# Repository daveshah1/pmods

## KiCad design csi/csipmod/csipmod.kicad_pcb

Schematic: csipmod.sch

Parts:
C1, C3: 1µ; C_0805_2012Metric
C2: 100p; C_0402_1005Metric
C4: 10µ; C_0805_2012Metric
J1: PMOD_1A; PMOD_2x06_2.54mm
J2: PMOD_1B; PMOD_2x06_2.54mm
P1: PICAM; 1-1734248-5
R1, R2, R4, R5, R25: 10k; R_0402_1005Metric
R3: 200k; R_0402_1005Metric
R6, R10, R13, R14, R17, R18, R19, R20, R21, R22, R23: DNP; R_0402_1005Metric
R7, R8, R11, R12, R15, R16: 0; R_0402_1005Metric
R9: 220; R_0402_1005Metric
R24: 33k; R_0402_1005Metric
R26, R27, R28: 100; R_0402_1005Metric
R29: 0R; R_0805_2012Metric
U1: LD3985M18R_SOT23; SOT-23-5
U2: PCA9306; SSOP-8_2.95x2.8mm_P0.65mm

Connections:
+1V8: C3.1, R1.1, R2.1, U1.5 (VOUT), U2.2
+3V3: C1.1, J1.6, J1.12, J2.6, J2.12, R3.1, R4.1, R5.1, R24.1, R29.2, U1.1 (VIN), U1.3 (INH)
/CAM_ENABLE: J1.7, P1.11
/CAM_SCL: P1.13, R1.2, U2.3
/CAM_SDA: P1.14, R2.2, U2.4
/CCLK+: P1.9, R16.1, R17.2, R23.1, R28.2
/CCLK-: P1.8, R14.1, R15.1, R22.2, R28.1
/CD0+: P1.3, R8.1, R9.2, R19.1, R26.2
/CD0-: P1.2, R6.1, R7.1, R18.2, R26.1
/CD1+: P1.6, R12.1, R13.2, R21.1, R27.2
/CD1-: P1.5, R10.1, R11.1, R20.2, R27.1
/FPGA_SCL: J2.10, R4.2, U2.6
/FPGA_SDA: J2.3, R5.2, U2.5
/HSCLK+: J2.9, R16.2
/HSCLK-: J2.4, R15.2
/HSD0+: J2.7, R8.2
/HSD0-: J2.2, R7.2
/HSD1+: J2.8, R12.2
/HSD1-: J2.1, R11.2
/LPCLK+: J1.2, R17.1
/LPCLK-: J1.1, R14.2
/LPD0+: J1.4, R9.1
/LPD0-: J1.3, R6.2
/LPD1+: J1.10, R13.1
/LPD1-: J1.9, R10.2
/LPDREF: J1.8, R24.2, R25.1
GND: C1.2, C2.2, C3.2, C4.2, J1.5, J1.11, J2.5, J2.11, P1.1, P1.4, P1.7, P1.10, R18.1, R19.2, R20.1, R21.2, R22.1, R23.2, R25.2, U1.2 (GND), U2.1
unnamed: C2.1, R3.2, U2.7, U2.8
unnamed: C4.1, P1.15, R29.1

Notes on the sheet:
*DNP
*51
*120
*22
NOTE Default values are for camera --> FPGA Values with * are for FPGA --> Pi
PMODs pairs for icebreaker use only

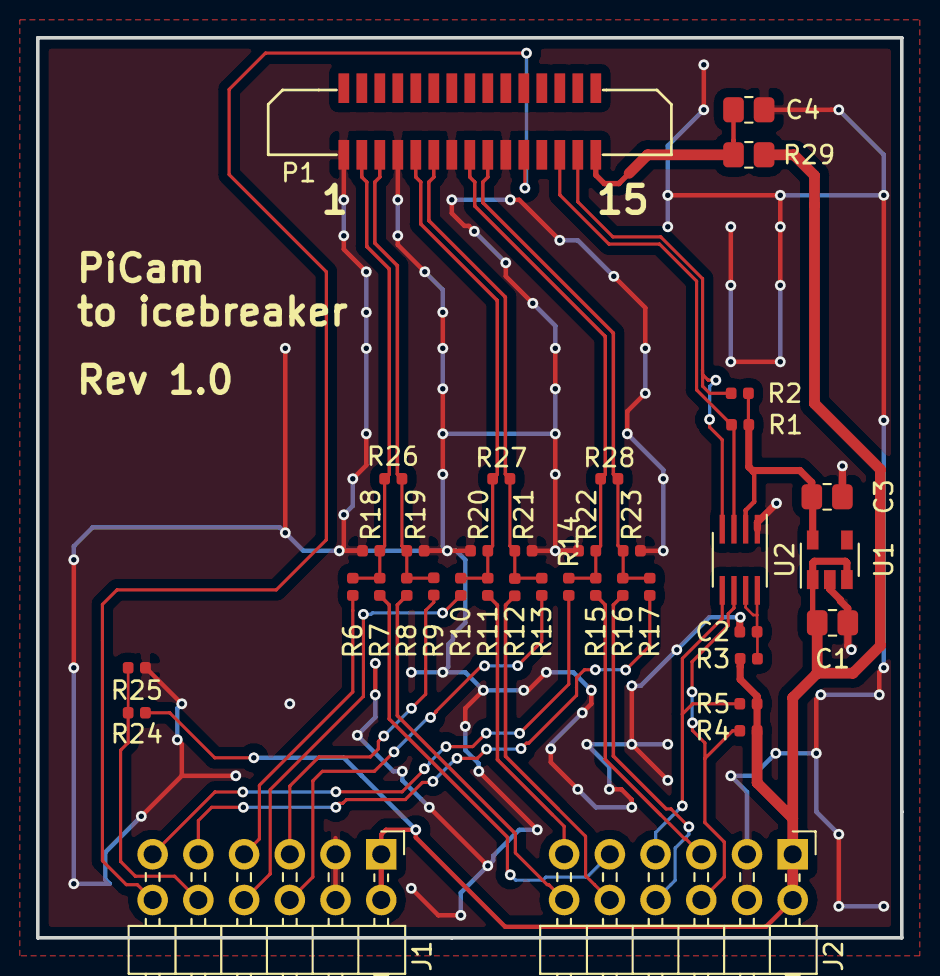
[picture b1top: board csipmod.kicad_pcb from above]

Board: 4 copper layers, 48.0 x 50.0 mm, 38 parts (0 on the bottom side), 29 nets.

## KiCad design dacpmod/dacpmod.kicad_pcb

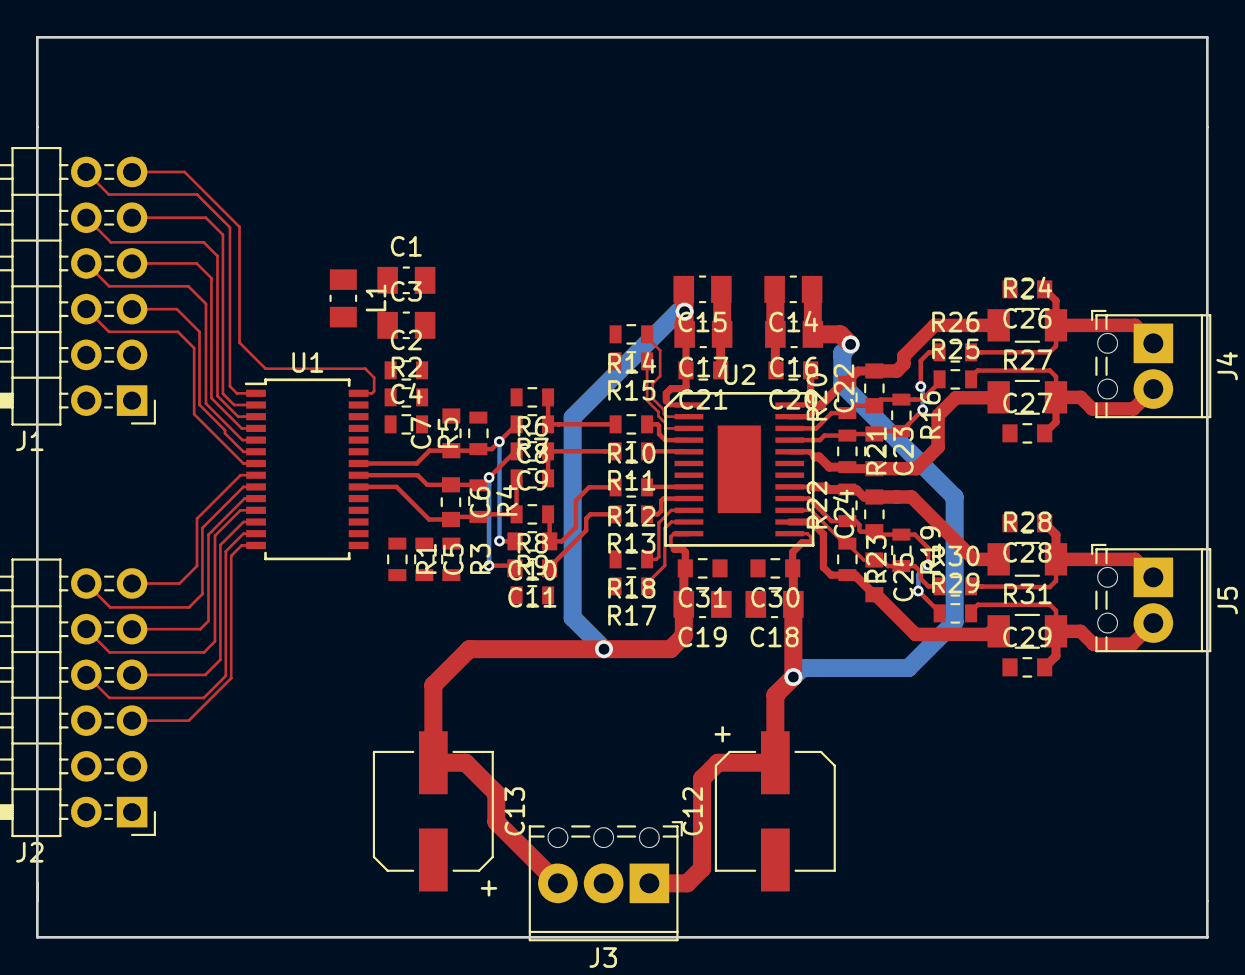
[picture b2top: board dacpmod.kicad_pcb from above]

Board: 2 copper layers, 65.0 x 50.0 mm, 71 parts (1 on the bottom side), 51 nets.

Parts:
C1, C3: 4.7µ; C_0805_2012Metric_Pad1.15x1.50mm_HandSolder
C2, C4, C5, C8, C9: 100n; C_0603_1608Metric
C6, C7, C10, C11, C22, C23, C24, C25, C26, C27, C28, C29: DNP; C_0603_1608Metric_Pad0.84x1.00mm_HandSolder
C12, C13: 100u; CP_Elec_6.3x5.8
C14, C15: 1µ; C_0805_2012Metric_Pad1.15x1.50mm_HandSolder
C16, C17, C18, C19: 100n; C_0805_2012Metric_Pad1.15x1.50mm_HandSolder
C20, C21, C30, C31: 10n; C_0603_1608Metric_Pad0.84x1.00mm_HandSolder
J1: PMOD1; PMOD_2x06_2.54mm
J2: PMOD2; PMOD_2x06_2.54mm
J3: POWER; TerminalBlock_Phoenix_MPT-0,5-3-2.54_1x03_P2.54mm_Horizontal
J4, J5: OUT; TerminalBlock_Phoenix_MPT-0,5-2-2.54_1x02_P2.54mm_Horizontal
L1: L_Small; L_0805_2012Metric_Pad1.15x1.50mm_HandSolder
R1, R2, R3: 10k; R_0603_1608Metric
R4, R5: 50; R_0603_1608Metric
R6, R7, R8, R9, R20, R21, R22, R23: 2k; R_0603_1608Metric
R10, R11, R12, R13: 20; R_0603_1608Metric
R14, R15: 0R; R_0603_1608Metric
R16, R19: 1.33k; R_0603_1608Metric
R17, R18: DNP; R_0603_1608Metric
R24, R27, R28, R31: 9R1; R_1206_3216Metric_Pad1.24x1.80mm_HandSolder
R25, R26, R29, R30: 2.7k; R_0603_1608Metric
TP1: Iadj; TestPoint_Pad_D2.0mm
U1: AD9744; TSSOP-28_4.4x9.7mm_P0.65mm
U2: THS6024; TI-PowerSO24

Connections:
+3V3: C1.1, C2.1, J1.6, J1.12, J2.6, J2.12, L1.1, U1.27
/CLK: J1.1, U1.28
/D0: J2.4, U1.14
/D1: J2.9, U1.13
/D2: J2.3, U1.12
/D3: J2.8, U1.11
/D4: J2.2, U1.10
/D5: J2.7, U1.9
/D6: J2.1, U1.8
/D7: J1.10, U1.7
/D8: J1.4, U1.6
/D9: J1.9, U1.5
/D10: J1.3, U1.4
/D11: J1.8, U1.3
/D12: J1.2, U1.2
/D13: J1.7, U1.1
GND: C1.2, C2.2, C3.2, C4.2, C5.2, C6.2, C7.2, C12.2, C13.1, C14.2, C15.1, C16.2, C17.1, C18.2, C19.1, C20.2, C21.1, C26.2, C27.1, C28.2, C29.1, C30.2, C31.1, J1.5, J1.11, J2.5, J2.11, J3.2, R1.2, R2.2, R3.2, R4.2, R5.2, R6.2, R7.1, R8.2, R9.1, R14.2, R15.2, R17.2, R18.2, U1.16, U1.20, U1.26, U2.6, U2.25
unnamed: C3.1, C4.1, L1.2, U1.24
unnamed: C5.1, U1.17
unnamed: C8.1, R6.1, R10.2
unnamed: C9.1, R7.2, R11.2
unnamed: C10.1, R8.1, R12.2
unnamed: C7.1, C8.2, C10.2, R5.1, U1.22
unnamed: C11.1, R9.2, R13.2
unnamed: C6.1, C9.2, C11.2, R4.1, U1.21
unnamed: C22.1, R16.1, R20.1, R25.1, U2.22
unnamed: C22.2, R20.2, R24.1, U2.23
unnamed: C23.1, R16.2, R21.1, R26.1, U2.21
unnamed: C23.2, R21.2, R27.1, U2.20
unnamed: C24.1, R19.1, R22.1, R29.1, U2.16
unnamed: C24.2, R22.2, R28.1, U2.17
unnamed: C25.1, R19.2, R23.1, R30.1, U2.15
unnamed: C25.2, R23.2, R31.1, U2.14
unnamed: C26.1, J4.1, R24.2, R26.2
unnamed: C27.2, J4.2, R25.2, R27.2
unnamed: C28.1, J5.1, R28.2, R30.2
unnamed: C29.2, J5.2, R29.2, R31.2
unnamed: R1.1, U1.15
unnamed: R2.1, U1.25
unnamed: R3.1, U1.18
unnamed: R10.1, U2.4
unnamed: R11.1, U2.5
unnamed: R12.1, U2.8
unnamed: R13.1, U2.9
unnamed: R14.1, U2.2
unnamed: R15.1, U2.3
unnamed: R17.1, U2.11
unnamed: R18.1, U2.10
unnamed: TP1.1, U2.7
VCC: C12.1, C14.1, C16.1, C18.1, C20.1, C30.1, J3.1, U2.13, U2.24
VEE: C13.2, C15.2, C17.2, C19.2, C21.2, C31.2, J3.3, U2.1, U2.12

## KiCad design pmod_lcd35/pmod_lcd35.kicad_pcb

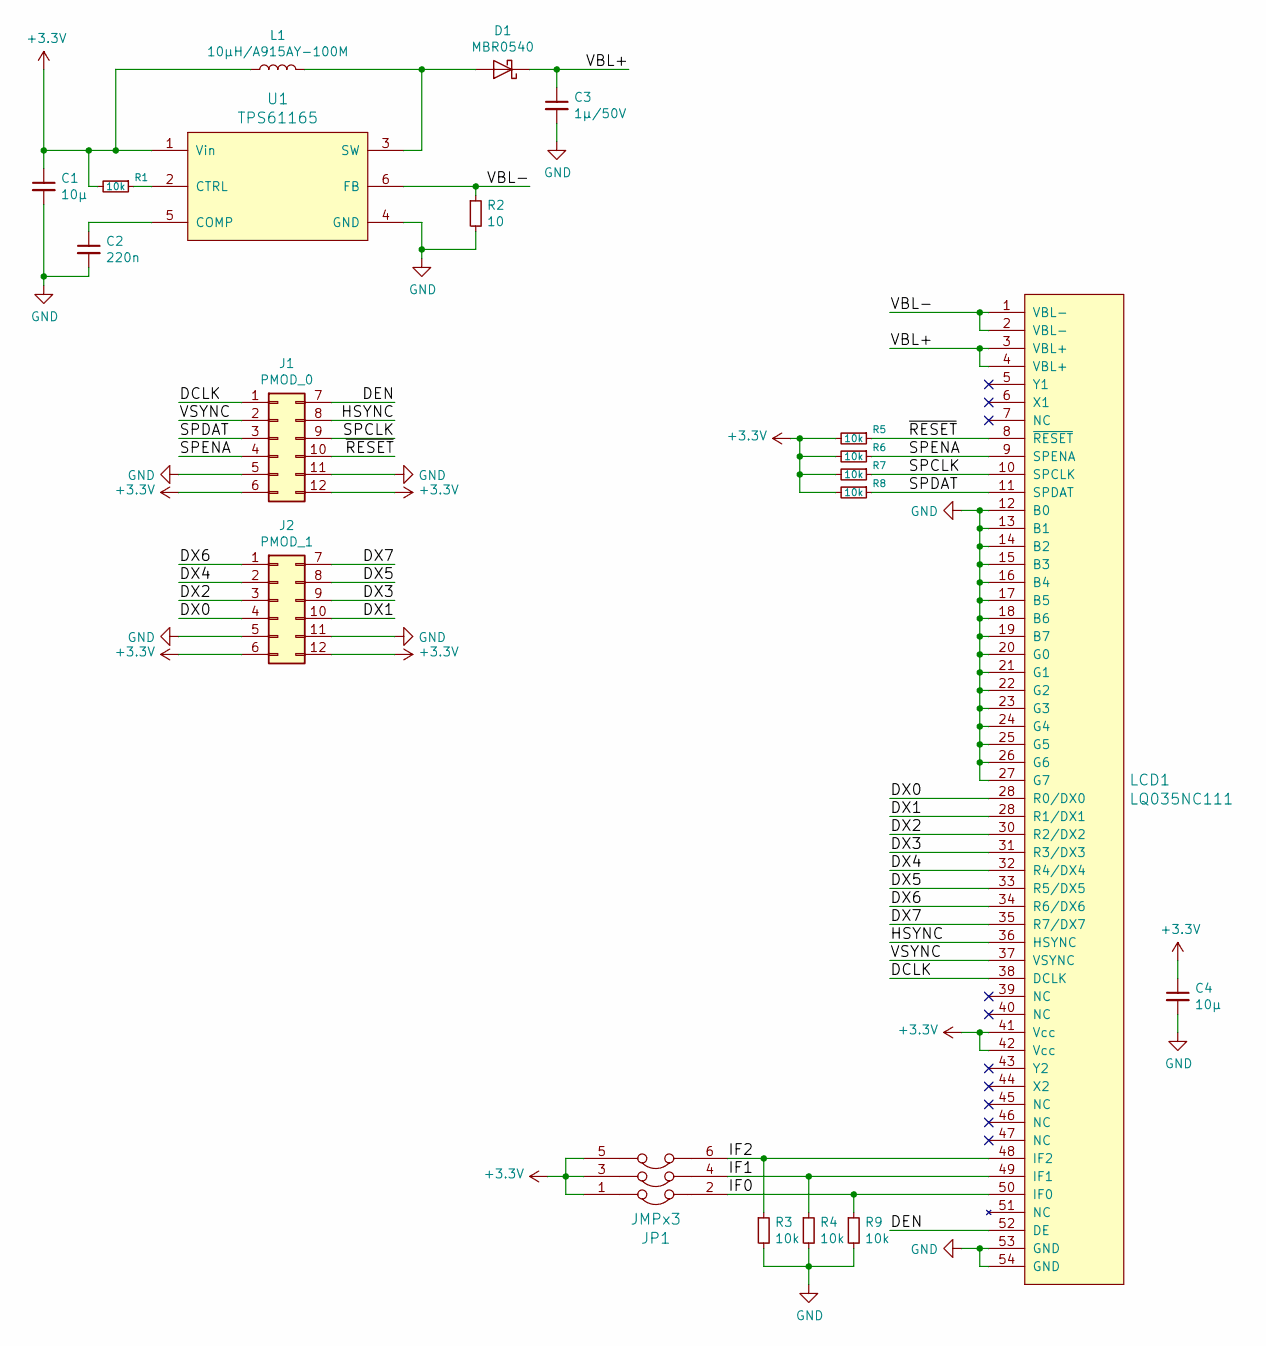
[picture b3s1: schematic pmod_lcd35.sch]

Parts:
C1, C4: 10µ; C_0805
C2: 220n; C_0603
C3: 1µ/50V; C_0805
D1: MBR0540; D_SOD-123
J1: PMOD_0; PMOD_2x06_2.54mm
J2: PMOD_1; PMOD_2x06_2.54mm
JP1: JMPx3; Pin_Header_Straight_2x03_Pitch2.54mm
L1: 10µH/A915AY-100M; muRata_L_2020
LCD1: LQ035NC111; MOLEX_51296-5494_54pin_0.5mm_BTM
R1, R3, R4, R5, R6, R7, R8, R9: 10k; R_0603
R2: 10; R_0603
U1: TPS61165; SOT-23-6

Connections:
+3V3: C1.1, C4.1, J1.6, J1.12, J2.6, J2.12, JP1.1, JP1.3, JP1.5, L1.1, LCD1.41 (Vcc), LCD1.42 (Vcc), R1.2, R5.2, R6.2, R7.2, R8.2, U1.1 (Vin)
/DCLK: J1.1, LCD1.38 (DCLK)
/DEN: J1.7, LCD1.52 (DE)
/DX2: J2.3, LCD1.30 (R2/DX2)
/DX3: J2.9, LCD1.31 (R3/DX3)
/DX4: J2.2, LCD1.32 (R4/DX4)
/DX5: J2.8, LCD1.33 (R5/DX5)
/DX6: J2.1, LCD1.34 (R6/DX6)
/DX7: J2.7, LCD1.35 (R7/DX7)
/HSYNC: J1.8, LCD1.36 (HSYNC)
/IF0: JP1.2, LCD1.50 (IF0), R9.1
/IF1: JP1.4, LCD1.49 (IF1), R4.1
/IF2: JP1.6, LCD1.48 (IF2), R3.1
/SPCLK: J1.9, LCD1.10 (SPCLK), R7.1
/SPDAT: J1.3, LCD1.11 (SPDAT), R8.1
/SPENA: J1.4, LCD1.9 (SPENA), R6.1
/VBL+: C3.1, D1.1 (K), LCD1.3 (VBL+), LCD1.4 (VBL+)
/VBL-: LCD1.1 (VBL-), LCD1.2 (VBL-), R2.1, U1.6 (FB)
/VSYNC: J1.2, LCD1.37 (VSYNC)
/~RESET: J1.10, LCD1.8 (~RESET), R5.1
GND: C1.2, C2.2, C3.2, C4.2, J1.5, J1.11, J2.5, J2.11, LCD1.12 (B0), LCD1.13 (B1), LCD1.14 (B2), LCD1.15 (B3), LCD1.16 (B4), LCD1.17 (B5), LCD1.18 (B6), LCD1.19 (B7), LCD1.20 (G0), LCD1.21 (G1), LCD1.22 (G2), LCD1.23 (G3), LCD1.24 (G4), LCD1.25 (G5), LCD1.26 (G6), LCD1.27 (G7), LCD1.53 (GND), LCD1.54 (GND), R2.2, R3.2, R4.2, R9.2, U1.4 (GND)
unnamed: C2.1, U1.5 (COMP)
unnamed: D1.2 (A), L1.2, U1.3 (SW)
unnamed: R1.1, U1.2 (CTRL)

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
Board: 2 copper layers, 20 parts (0 on the bottom side), 25 nets, no tracks yet.

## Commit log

2018-01-01 Initial schematic for LCD pmod
2018-01-01 LCD PMOD PCB ready to route
2018-01-01 LCD PMOD PCB routed
2018-01-28 Working LCD demo
2018-05-07 Adding DAC+VDSL PMOD
2018-05-07 DAC+VDSL PMOD placed
2018-05-08 DAC+VDSL PMOD routed
2018-07-15 csipmod: Schematics for icebreaker <-> CSI-2 PMOD
2018-07-15 csipmod: PCB ready to route
2018-07-15 csipmod: Routed
2018-08-08 Adding CSI schematic and gerbers
2019-09-19 works with icebreaker
2019-09-19 fix makefile
